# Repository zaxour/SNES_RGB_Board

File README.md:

# SNES_RGB_Board
ERRATA:
R4 and R5 should be changed to 4.99k. 

Remix of Borti's ubiquitous SNES RGB board with S-video restoration.

Certain components, such as the 47 pF caps on the output were left out. LPF is disabled by default; connecting the jumper will enable it.

.brd/.sch files provided for Eagle PCB (Fusion 360). Gerbers provided in the zip file.

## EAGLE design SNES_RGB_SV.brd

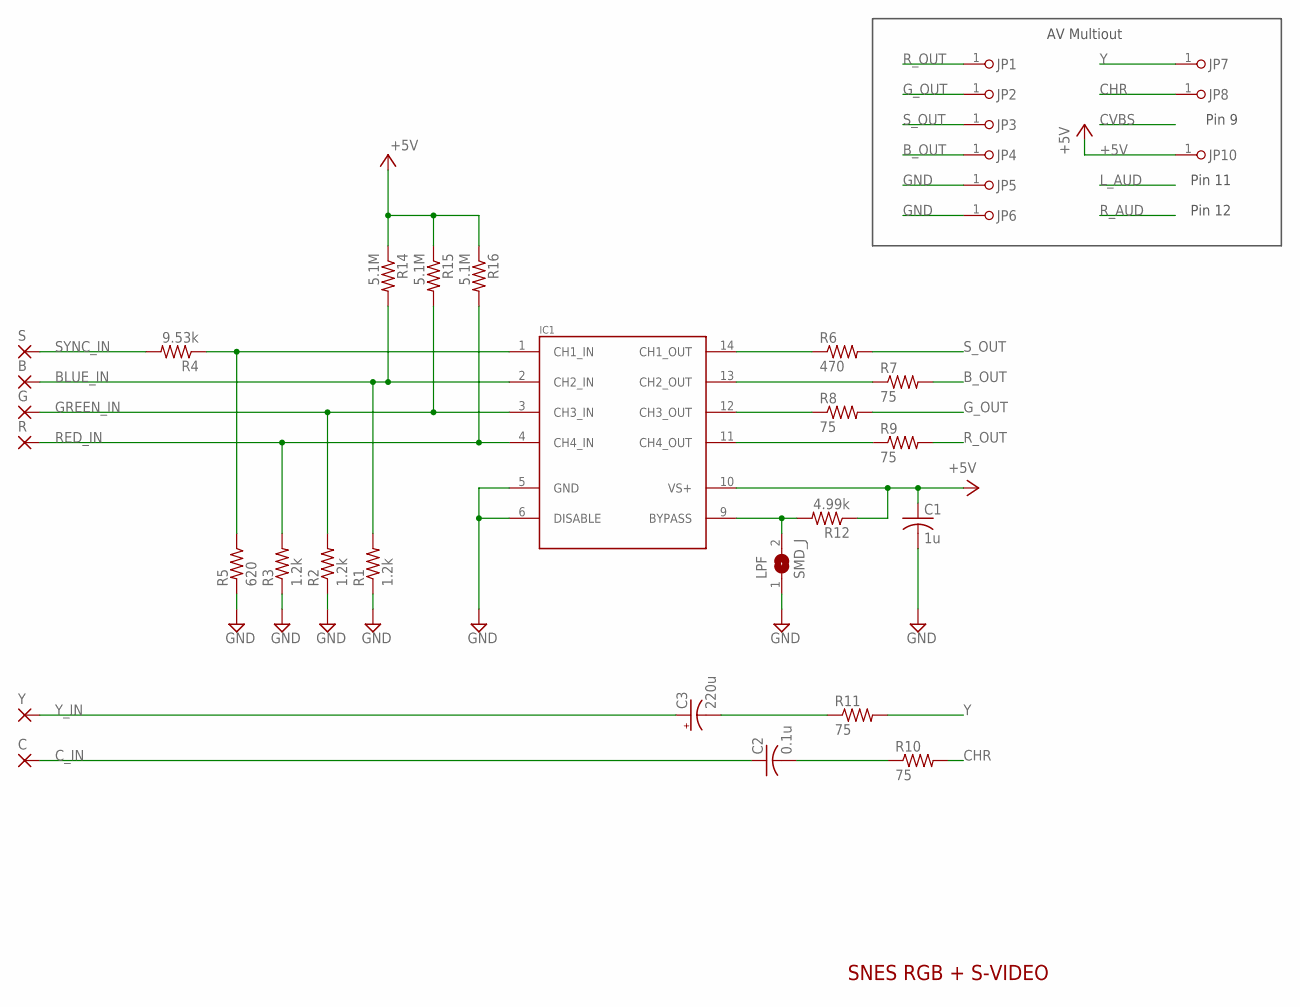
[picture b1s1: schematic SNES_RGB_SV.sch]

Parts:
B: SMD2; SMD1,27-2,54
C: SMD2; SMD1,27-2,54
C1: 1u; C0603
C2: 0.1u; C0603
C3: 220u; C/6032-28R
G: SMD2; SMD1,27-2,54
IC1: THS7374IPWR; TSSOP14
JP1, JP2, JP3, JP4, JP5, JP6, JP7, JP8, JP10: PINHD-1X1; 1X01
LPF: SMD_J; SJ
R: SMD2; SMD1,27-2,54
R1, R2, R3: 1.2k; R0603
R4: 9.53k; R0603
R5: 620; R0603
R6: 470; R0603
R7, R8, R9, R10, R11: 75; R0603
R12: 4.99k; R0603
R14, R15, R16: 5.1M; R0603
S: SMD2; SMD1,27-2,54
Y: SMD2; SMD1,27-2,54

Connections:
+5V: C1.1, IC1.10 (VS+), JP10.1, R12.1, R14.1, R15.1, R16.1
BLUE_IN: B.1, IC1.2 (CH2_IN), R1.2, R14.2
B_OUT: JP4.1, R7.2
CHR: JP8.1, R10.2
C_IN: C.1, C2.1
GND: C1.2, IC1.5 (GND), IC1.6 (DISABLE), JP5.1, JP6.1, LPF.1, R1.1, R2.1, R3.1, R5.2
GREEN_IN: G.1, IC1.3 (CH3_IN), R2.2, R15.2
G_OUT: JP2.1, R8.2
unnamed: IC1.1 (CH1_IN), R4.1, R5.1
unnamed: IC1.9 (BYPASS), LPF.2, R12.2
unnamed: IC1.14 (CH1_OUT), R6.1
unnamed: IC1.13 (CH2_OUT), R7.1
unnamed: IC1.12 (CH3_OUT), R8.1
unnamed: IC1.11 (CH4_OUT), R9.1
unnamed: C2.2, R10.1
unnamed: C3.-, R11.1
RED_IN: IC1.4 (CH4_IN), R.1, R3.2, R16.2
R_OUT: JP1.1, R9.2
SYNC_IN: R4.2, S.1
S_OUT: JP3.1, R6.2
Y: JP7.1, R11.2
Y_IN: C3.+, Y.1

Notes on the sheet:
Pin 9
Pin 11
Pin 12
AV Multiout
SNES RGB + S-VIDEO

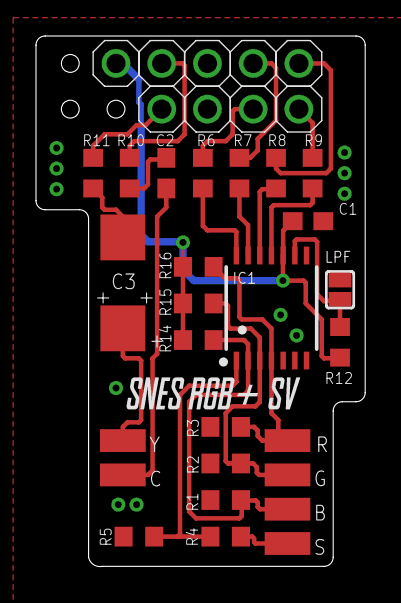
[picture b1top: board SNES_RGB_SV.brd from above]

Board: 2 copper layers, 18.3 x 29.5 mm, 35 parts (0 on the bottom side), 22 nets.

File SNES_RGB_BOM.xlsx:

Qty | Value | Package |  | Parts | Cost Each | Extended | Description
1 | 0.1u | C0603 | v | C2 | 1.2999999999999999E-2 | 1.2999999999999999E-2 | CAPACITOR, American symbol
3 | 1.2k | R0603 | v | R1, R2, R3 | 1.6E-2 | 4.8000000000000001E-2 | RESISTOR, American symbol
1 | 1u | C0603 | v | C1 | 1.7000000000000001E-2 | 1.7000000000000001E-2 | CAPACITOR, American symbol
1 | 220u | CT6032 | v | C3 | 0.67 | 0.67 | POLARIZED CAPACITOR, American symbol
1 | 4.99k | R0603 | v 4.7k | R12 | 2.4E-2 | 2.4E-2 | RESISTOR, American symbol
1 | 470 | R0603 | v | R6 | 1.6E-2 | 1.6E-2 | RESISTOR, American symbol
3 | 5.1M | R0603 | v | R14, R15, R16 | 1.6E-2 | 4.8000000000000001E-2 | RESISTOR, American symbol
1 | 620 | R0603 | v | R5 | 1.6E-2 | 1.6E-2 | RESISTOR, American symbol
3 | 75 | R0603 | v | R7, R8, R9,R10, R11 | 2.4E-2 | 7.2000000000000008E-2 | RESISTOR, American symbol
1 | 9.53k | R0603 | v | R4 | 7.0000000000000001E-3 | 7.0000000000000001E-3 | RESISTOR, American symbol
1 | THS7374IPWR | TSSOP14 |  | U$1 | 0.53 | 0.53
 |  |  |  |  | TOTAL | 1.4610000000000003
